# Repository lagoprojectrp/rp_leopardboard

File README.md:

# rp_leopardboard
Stackable shield for Red Pitaya open instrument.

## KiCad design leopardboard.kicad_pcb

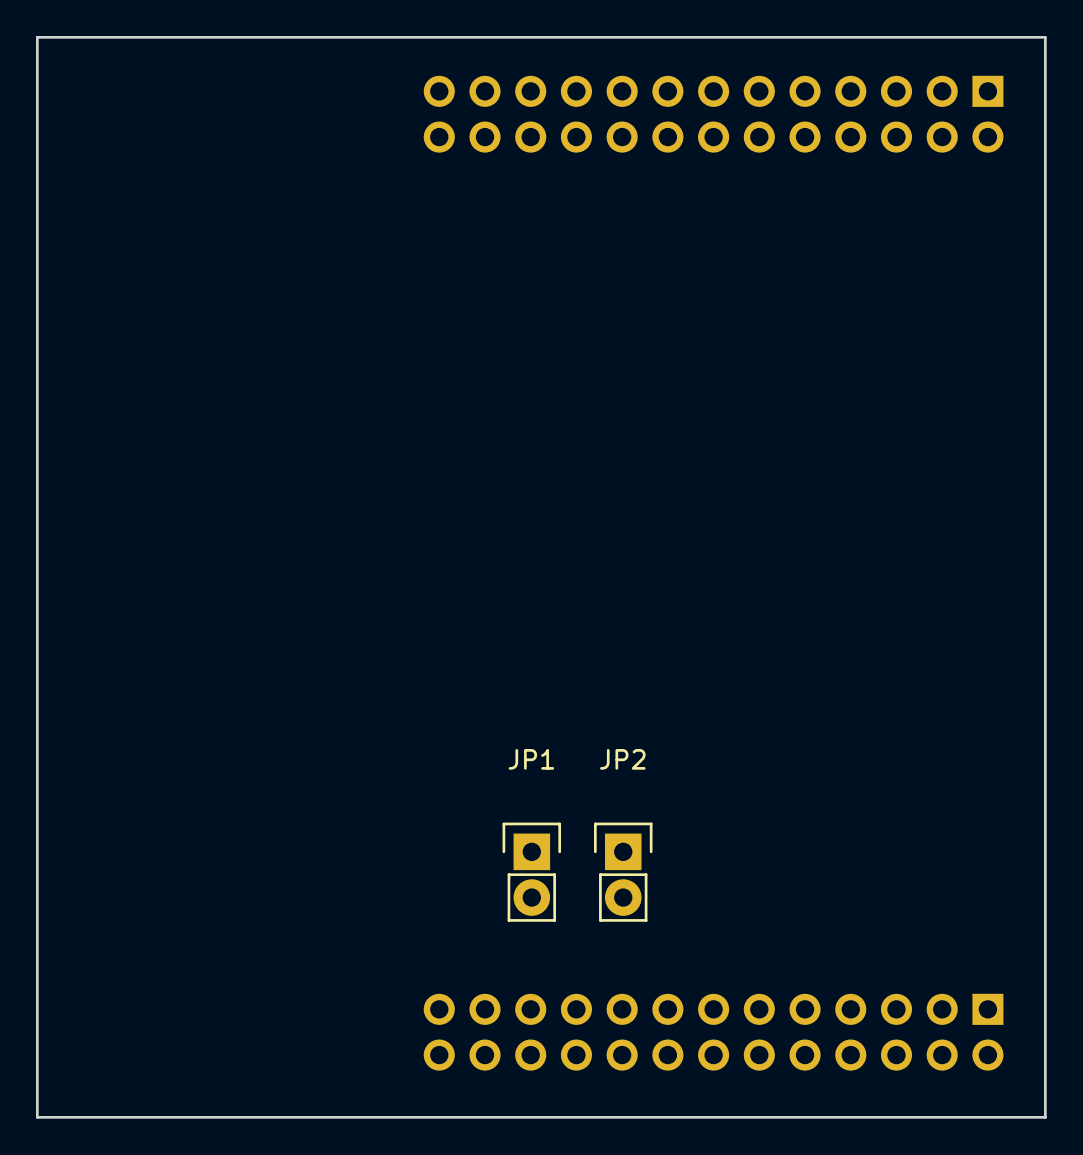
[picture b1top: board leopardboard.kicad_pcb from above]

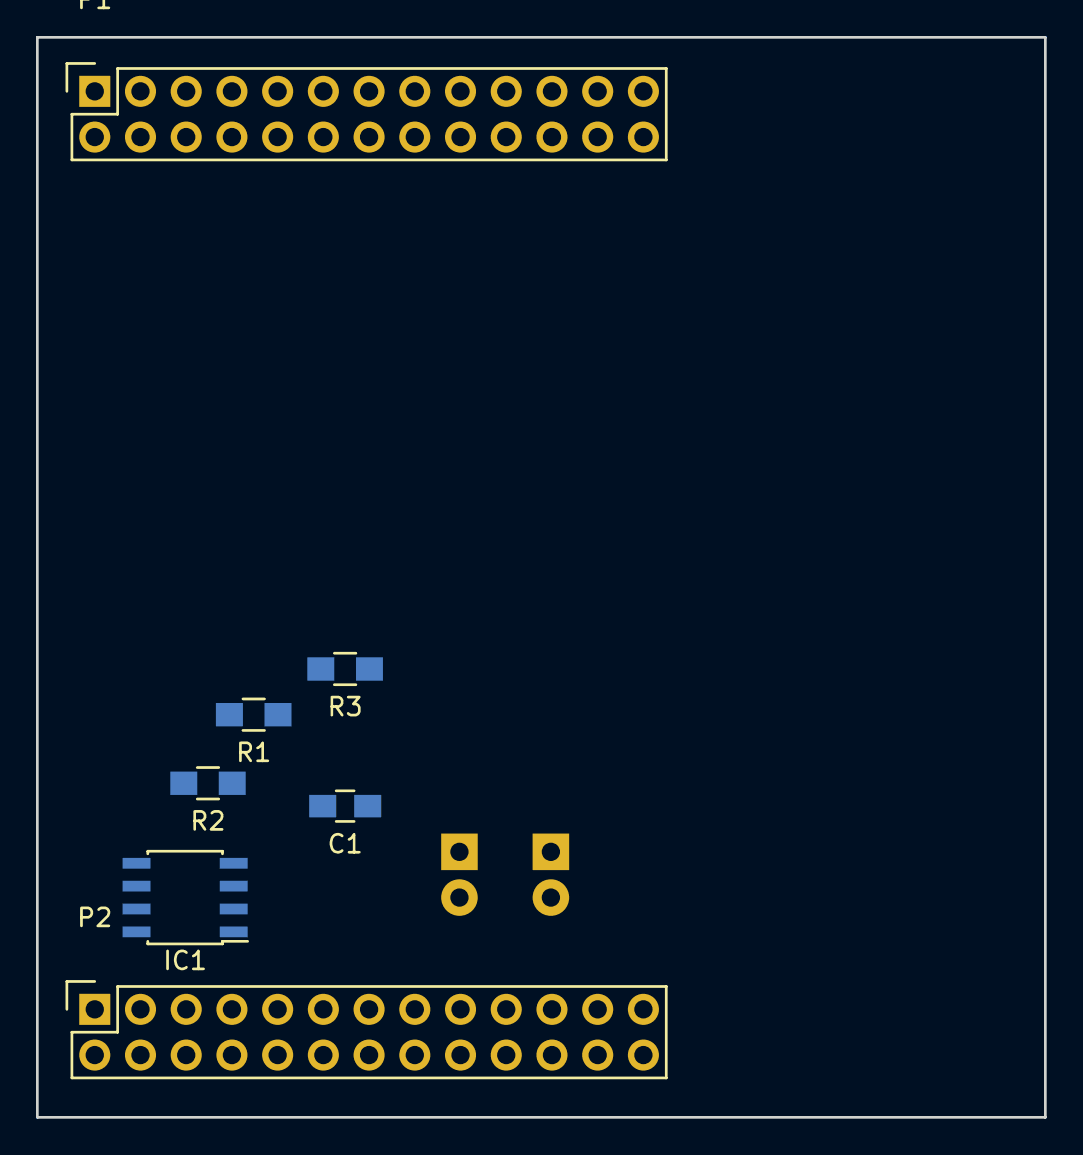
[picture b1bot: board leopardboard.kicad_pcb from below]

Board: 2 copper layers, 56.0 x 60.0 mm, 9 parts (7 on the bottom side), 6 nets, no tracks yet.

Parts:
C1: 100n; C_0805_HandSoldering
IC1: AT24LC64-I/SN; SOIC-8_3.9x4.9mm_Pitch1.27mm
JP1, JP2: JUMPER; Pin_Header_Straight_1x02
P1, P2: CONN_02X13; Socket_Strip_Straight_2x13
R1, R2, R3: 10k; R_0805_HandSoldering

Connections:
+3V3D: IC1.1, IC1.8, P2.1, P2.2, R1.1, R2.1, R3.1
GND: C1.2, IC1.2, IC1.3, IC1.4, JP1.2, JP2.2, P1.12, P1.21, P1.22, P1.25, P1.26, P2.25, P2.26
I2C0_SCL: IC1.6, R3.2
I2C0_SDA: IC1.5, R2.2
unnamed: IC1.7, JP1.1, R1.2
unnamed: JP2.1, P1.11

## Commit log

2016-05-06 New files added.
